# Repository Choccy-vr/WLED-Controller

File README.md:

# WLED-Controller
An all-in-one controller for WS2812B LED strips, made for WLED. With Adapters for LEDs everywhere.

I made this because these WS2812B strips and WLED look so good, but all the other WLED controllers are quite expensive, and I would rather make it by myself. I set out to make it as small as possible, even if that means making it harder for me.

On the controller PCB, I integrated basically a esp32 c3 supermini. That is the bulk of it, but I also put some capacitors on the LED PWR line for smoothing the power out. I also added a P-channel MOSFET to allow for a soft start.

The various adapter PCBs adapt the specified port into 5v and GND and output it to a USB-C, inspired by Framework's modules

### Images:

#### Schematic

#### Adapters
##### SATA Adapter

##### Barrel Jack Adapter

### BOM
|Product Name      |Product Description     |Product Link                                                                                          |Product unit price|Product amount|Product Cost|Total (Before Tax + Shipping)|Total |
|------------------|------------------------|------------------------------------------------------------------------------------------------------|------------------|--------------|------------|-----------------------------|------|
|Main PCB(A)       |The main control PCB    |https://jlcpcb.com/                                                                                   |$8.71             |5             |$35.45      |$59.27                       |$67.38|
|Sata Adapter PCB  |Sata adapter            |https://jlcpcb.com/                                                                                   |$1.02             |5             |$5.10       |                             |      |
|Barrel Adapter PCB|Barrel adapter          |https://jlcpcb.com/                                                                                   |$1.02             |5             |$5.10       |                             |      |
|Antenna           |Antenna                 |https://www.digikey.com/en/products/detail/pulse-electronics/ANT3216A063R2400A/3927186                |$0.22             |1             |$0.22       |                             |      |
|Bulk Cap          |Cap for LEDs            |https://www.digikey.com/en/products/detail/rubycon/35PX470MEFC10X12-5/3134236                         |$0.34             |10            |$3.44       |                             |      |
|Sata Connector    |Connector for SATA PCB  |https://www.digikey.com/en/products/detail/amphenol-cs-fci/10034814-001LF/1001349                     |$6.84             |1             |$6.84       |                             |      |
|USB-C             |Male USB C              |https://www.digikey.com/en/products/detail/same-sky-formerly-cui-devices/UP20-C-F-G-FL-P12-TR/24818610|$1.30             |2             |$2.60       |                             |      |
|Barrel Jack       |Connector for Barrel PCB|https://www.digikey.com/en/products/detail/same-sky-formerly-cui-devices/PJ-002A/96962                |$0.52             |1             |$0.52       |                             |      |

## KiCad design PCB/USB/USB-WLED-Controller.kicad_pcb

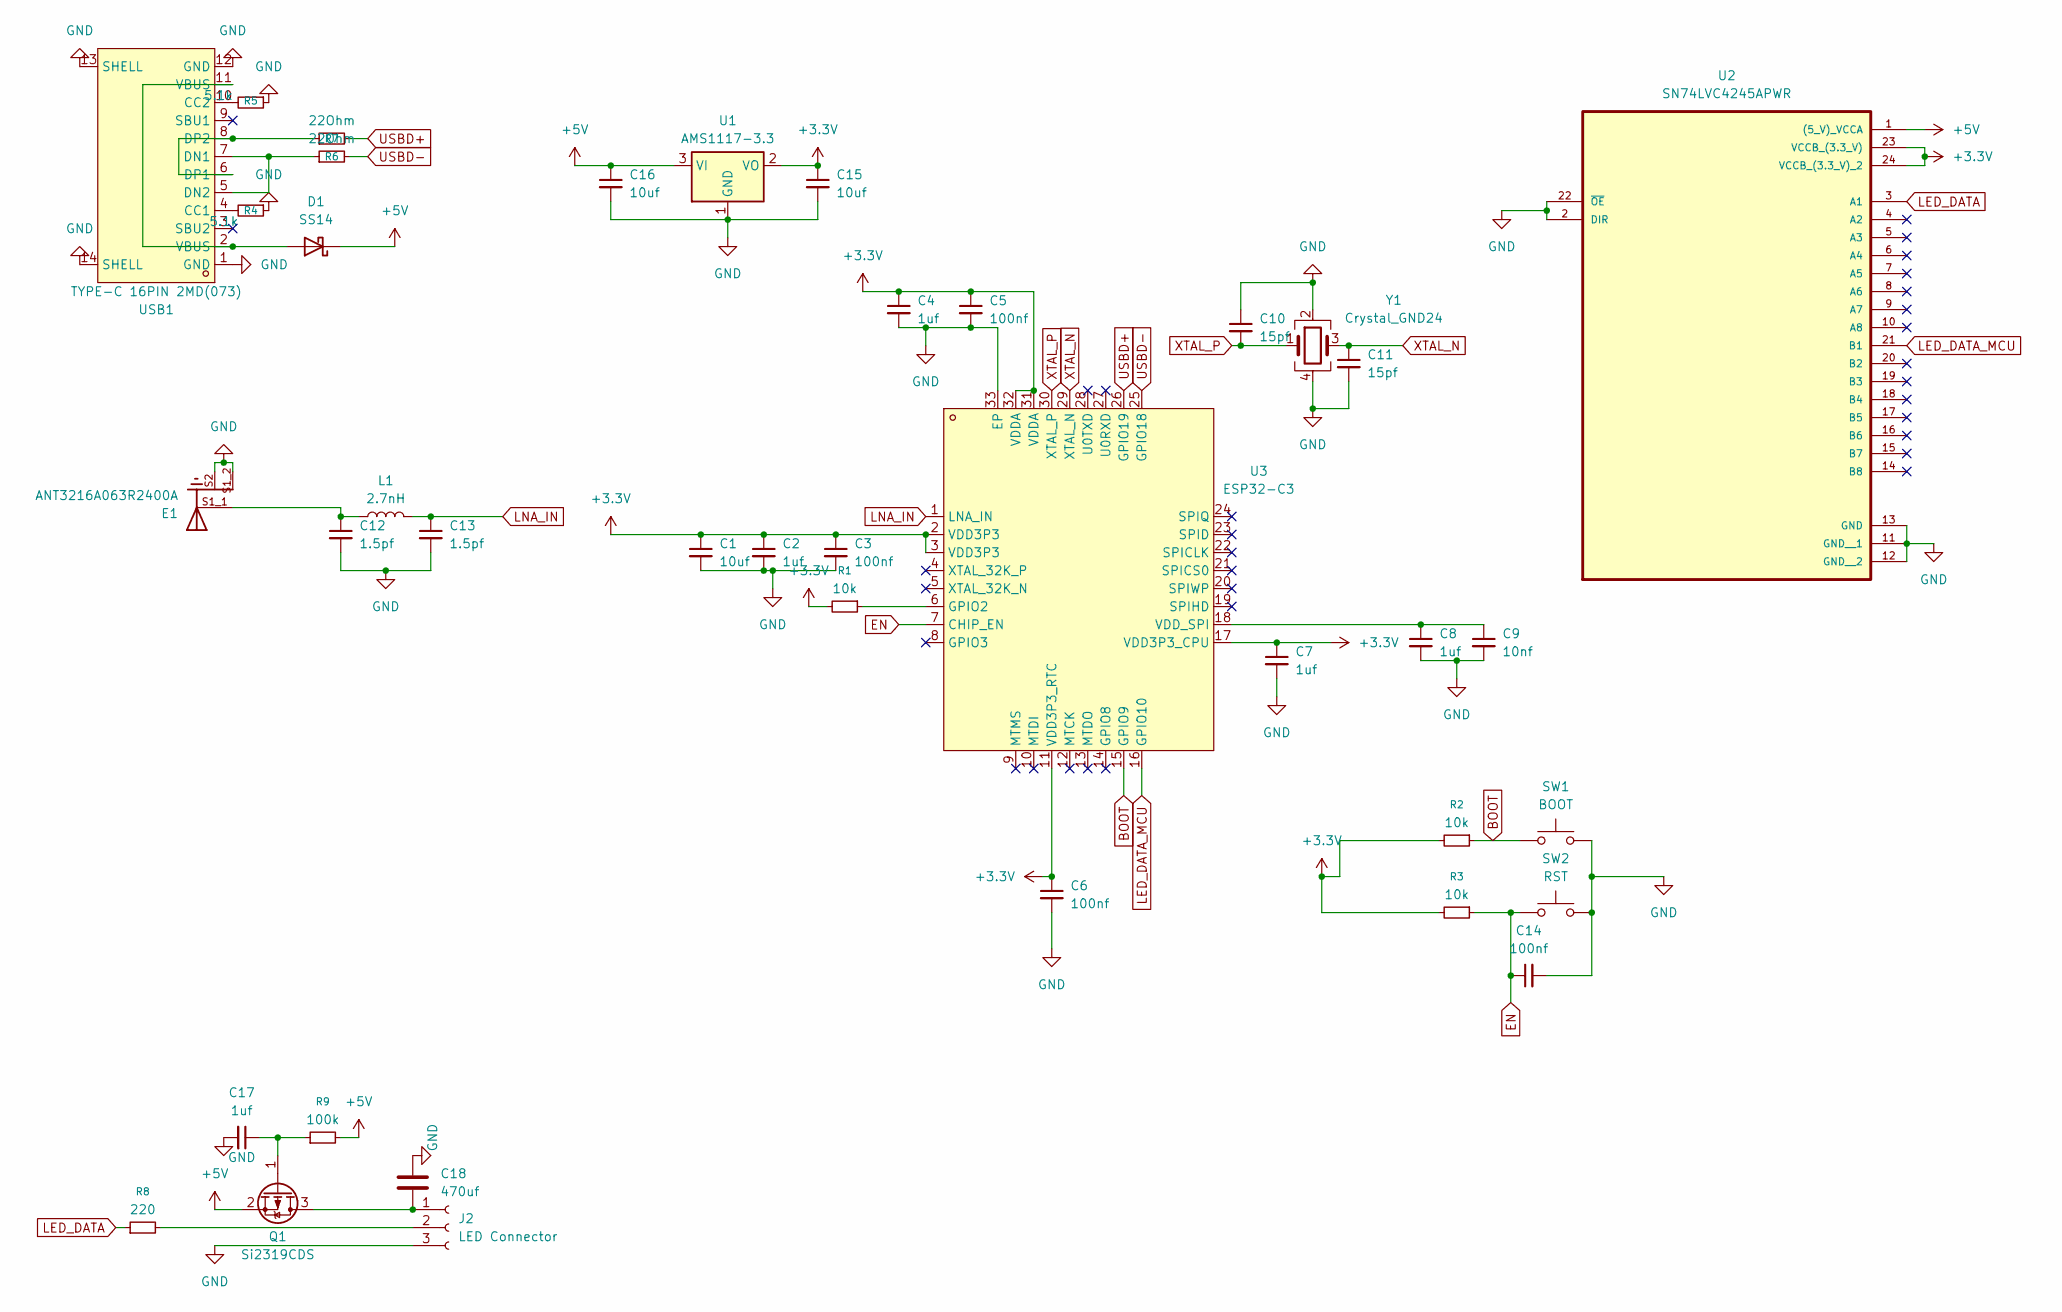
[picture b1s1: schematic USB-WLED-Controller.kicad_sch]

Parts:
C1, C15, C16: 10uf; C_0402_1005Metric; LCSC C15525
C2, C4, C7, C8, C17: 1uf; C_0402_1005Metric; LCSC C52923
C3, C5, C6, C14: 100nf; C_0402_1005Metric; LCSC C1525
C9: 10nf; C_0402_1005Metric; LCSC C15195
C10, C11: 15pf; C_0402_1005Metric; LCSC C1548
C12, C13: 1.5pf; C_0402_1005Metric; LCSC C1552
C18: 470uf; CP_Radial_D10.0mm_P5.00mm
D1: SS14; D_SMA; LCSC C2480
E1: ANT3216A063R2400A; XDCR_ANT3216A063R2400A; PARTREV 1
J2: LED Connector; PinSocket_1x03_P2.54mm_Vertical
L1: 2.7nH; L_0402_1005Metric; LCSC C27123
Q1: Si2319CDS; SOT-23; LCSC C10487
R1, R2, R3: 10k; R_0402_1005Metric; LCSC C25744
R4, R5: 5.1k; R_0402_1005Metric; LCSC C25905
R6, R7: 22Ohm; R_0402_1005Metric; LCSC C25092
R8: 220; R_0402_1005Metric; LCSC C25091
R9: 100k; R_0402_1005Metric; LCSC C25741
SW1: BOOT; SW_SPST_TS-1088-xR020; LCSC C720477
SW2: RST; SW_SPST_TS-1088-xR020; LCSC C720477
U1: AMS1117-3.3; SOT-223-3_TabPin2; LCSC C6186
U2: SN74LVC4245APWR; SOP65P640X120-24N; LCSC C7859
U3: ESP32-C3; QFN-32_L5.0-W5.0-P0.50-TL-EP3.7; LCSC Part C2838500
USB1: TYPE-C 16PIN 2MD(073); USB-C-SMD_TYPE-C-6PIN-2MD-073; LCSC Part C2765186
Y1: Crystal_GND24; Crystal_SMD_3225-4Pin_3.2x2.5mm; LCSC C252255

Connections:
+3.3V: C1.1, C2.1, C3.1, C4.1, C5.1, C6.1, C7.1, C15.1, R1.2, R2.2, R3.2, U1.2 (VO), U2.23 (VCCB_(3.3_V)), U2.24 (VCCB_(3.3_V)_2), U3.2 (VDD3P3), U3.3 (VDD3P3), U3.11 (VDD3P3_RTC), U3.17 (VDD3P3_CPU), U3.31 (VDDA), U3.32 (VDDA)
+5V: C16.1, D1.1 (K), Q1.2 (S), R9.2, U1.3 (VI), U2.1 ((5_V)_VCCA)
BOOT: R2.1, SW1.1, U3.15 (GPIO9)
EN: C14.1, R3.1, SW2.1, U3.7 (CHIP_EN)
GND: C1.2, C2.2, C3.2, C4.2, C5.2, C6.2, C7.2, C8.2, C9.2, C10.1, C11.2, C12.2, C13.2, C14.2, C15.2, C16.2, C17.2, C18.1, E1.S1_2, E1.S2, J2.3, R4.1, R5.1, SW1.2, SW2.2, U1.1 (GND), U2.2 (DIR), U2.11 (GND__1), U2.12 (GND__2), U2.13 (GND), U2.22 (~OE), U3.33 (EP), USB1.1 (GND), USB1.12 (GND), USB1.13 (SHELL), USB1.14 (SHELL), Y1.2, Y1.4
LED_DATA: R8.1, U2.3 (A1)
LED_DATA_MCU: U2.21 (B1), U3.16 (GPIO10)
LNA_IN: C13.1, L1.2, U3.1 (LNA_IN)
unnamed: C12.1, E1.S1_1, L1.1
unnamed: D1.2 (A), USB1.2 (VBUS), USB1.11 (VBUS)
unnamed: C18.2, J2.1, Q1.3 (D)
unnamed: J2.2, R8.2
unnamed: C17.1, Q1.1 (G), R9.1
unnamed: R1.1, U3.6 (GPIO2)
unnamed: C8.1, C9.1, U3.18 (VDD_SPI)
unnamed: R4.2, USB1.4 (CC1)
unnamed: R5.2, USB1.10 (CC2)
unnamed: R6.1, USB1.5 (DN2), USB1.7 (DN1)
unnamed: R7.1, USB1.6 (DP1), USB1.8 (DP2)
USBD+: R7.2, U3.26 (GPIO19)
USBD-: R6.2, U3.25 (GPIO18)
XTAL_N: C11.1, U3.29 (XTAL_N), Y1.3
XTAL_P: C10.2, U3.30 (XTAL_P), Y1.1

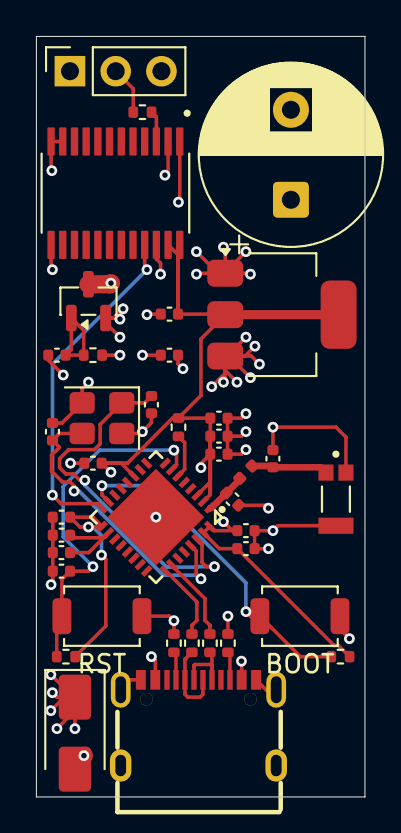
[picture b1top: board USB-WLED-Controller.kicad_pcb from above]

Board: 4 copper layers, 18.2 x 42.3 mm, 39 parts (0 on the bottom side), 23 nets.

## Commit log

2026-01-09 Enhance README with project details and BOM
    Expanded the README with additional details about the project, including images, adapters, and a bill of materials (BOM).
2026-01-09 Fix total cost for Main PCB(A) in README
    Updated total cost for Main PCB(A) in the BOM.
2026-01-11 Enhance README with additional project details
    Expanded the project description to include details about the PCB integration and adapter PCBs.
2026-01-11 Fix typos and improve readability in README.md
2026-01-23 Fix cost for Main PCB(A) in BOM
    Updated the total cost for Main PCB(A) in the BOM.
2026-01-23 Revise BOM with updated product costs and totals
    Updated product costs and totals in the BOM section.
